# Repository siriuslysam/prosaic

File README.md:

# Prosaic
A 71-key custom mechanical keyboard design with a layout that is essentially an ANSI TKL without F-keys.

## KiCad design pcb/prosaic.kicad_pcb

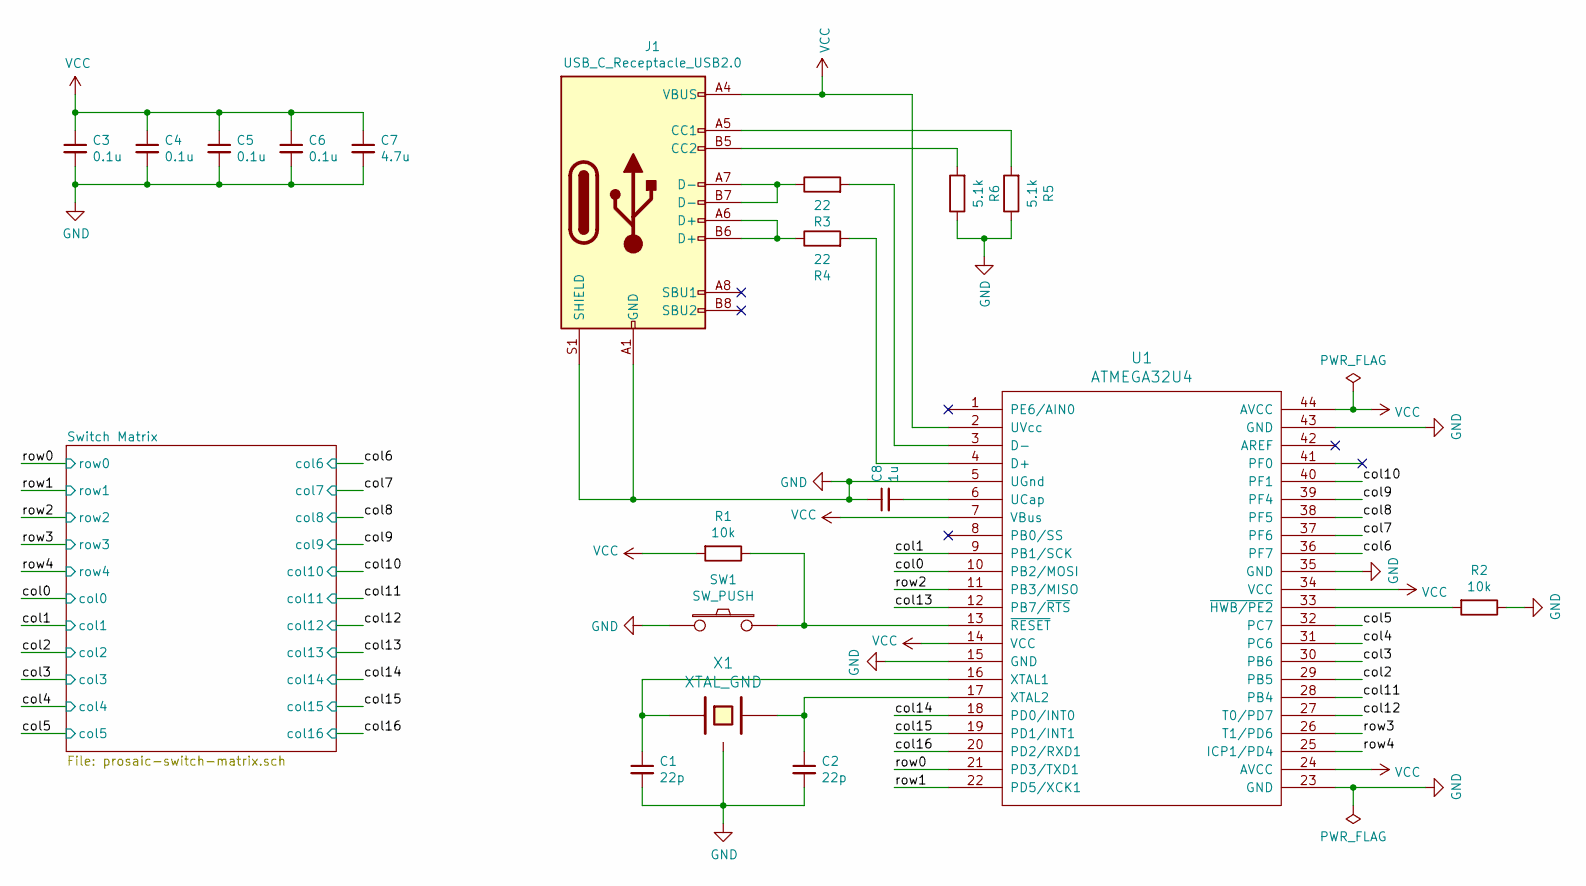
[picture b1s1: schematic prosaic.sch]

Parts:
C1, C2: 22p; C_0805_2012Metric_Pad1.15x1.40mm_HandSolder
C3, C4, C5, C6: 0.1u; C_0805_2012Metric_Pad1.15x1.40mm_HandSolder
C7: 4.7u; C_0805_2012Metric_Pad1.15x1.40mm_HandSolder
C8: 1u; C_0805_2012Metric_Pad1.15x1.40mm_HandSolder
J1: USB_C_Receptacle_USB2.0; USB_C_Receptacle_GCT_USB4085
R1, R2: 10k; R_0805_2012Metric_Pad1.15x1.40mm_HandSolder
R3, R4: 22; R_0805_2012Metric_Pad1.15x1.40mm_HandSolder
R5, R6: 5.1k; R_0805_2012Metric_Pad1.15x1.40mm_HandSolder
SW1: SW_PUSH; SW_SPST_TL3342
U1: ATMEGA32U4; TQFP-44_10x10mm_P0.8mm
X1: XTAL_GND; FA-238

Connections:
/col0: U1.10 (PB2/MOSI); also elsewhere on the board
/col1: U1.9 (PB1/SCK); also elsewhere on the board
/col2: U1.29 (PB5); also elsewhere on the board
/col3: U1.30 (PB6); also elsewhere on the board
/col4: U1.31 (PC6); also elsewhere on the board
/col5: U1.32 (PC7); also elsewhere on the board
/col6: U1.36 (PF7); also elsewhere on the board
/col7: U1.37 (PF6); also elsewhere on the board
/col8: U1.38 (PF5); also elsewhere on the board
/col9: U1.39 (PF4); also elsewhere on the board
/col10: U1.40 (PF1); also elsewhere on the board
/col11: U1.28 (PB4); also elsewhere on the board
/col12: U1.27 (T0/PD7); also elsewhere on the board
/col13: U1.12 (PB7/~RTS); also elsewhere on the board
/col14: U1.18 (PD0/INT0); also elsewhere on the board
/col15: U1.19 (PD1/INT1); also elsewhere on the board
/col16: U1.20 (PD2/RXD1); also elsewhere on the board
/row0: U1.21 (PD3/TXD1); also elsewhere on the board
/row1: U1.22 (PD5/XCK1); also elsewhere on the board
/row2: U1.11 (PB3/MISO); also elsewhere on the board
/row3: U1.26 (T1/PD6); also elsewhere on the board
/row4: U1.25 (ICP1/PD4); also elsewhere on the board
GND: C1.2, C2.2, C3.2, C4.2, C5.2, C6.2, C7.2, C8.1, J1.A1 (GND), J1.A12 (GND), J1.B1 (GND), J1.B12 (GND), J1.S1 (SHIELD), R2.1, R5.1, R6.1, SW1.1, U1.5 (UGnd), U1.15 (GND), U1.23 (GND), U1.35 (GND), U1.43 (GND), X1.3
unnamed: C1.1, U1.16 (XTAL1), X1.1
unnamed: C2.1, U1.17 (XTAL2), X1.2
unnamed: C8.2, U1.6 (UCap)
unnamed: J1.A5 (CC1), R5.2
unnamed: J1.A6 (D+), J1.B6 (D+), R4.1
unnamed: J1.A7 (D-), J1.B7 (D-), R3.1
unnamed: J1.B5 (CC2), R6.2
unnamed: R1.1, SW1.2, U1.13 (~RESET)
unnamed: R2.2, U1.33 (~HWB/PE2)
unnamed: R3.2, U1.3 (D-)
unnamed: R4.2, U1.4 (D+)
VCC: C3.1, C4.1, C5.1, C6.1, C7.1, J1.A4 (VBUS), J1.A9 (VBUS), J1.B4 (VBUS), J1.B9 (VBUS), R1.2, U1.2 (UVcc), U1.7 (VBus), U1.14 (VCC), U1.24 (AVCC), U1.34 (VCC), U1.44 (AVCC)

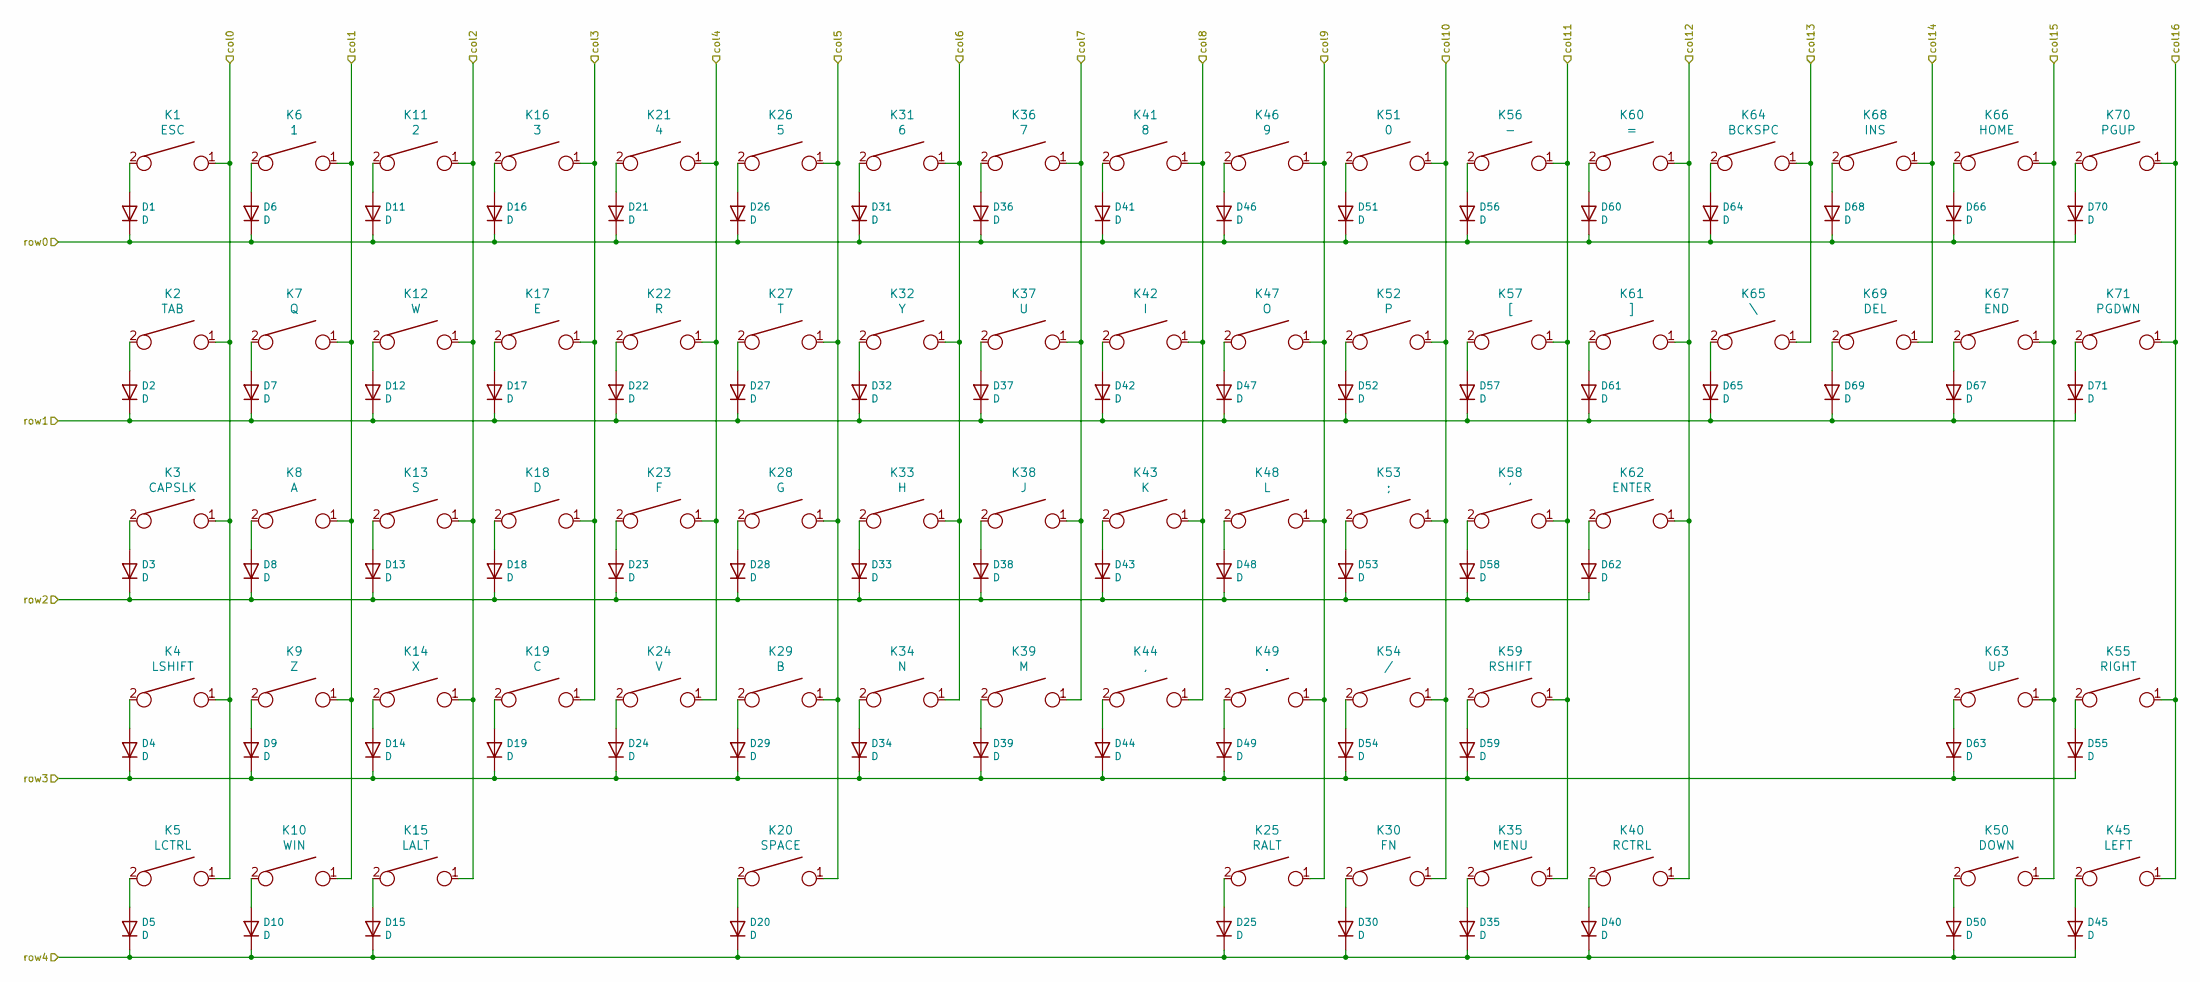
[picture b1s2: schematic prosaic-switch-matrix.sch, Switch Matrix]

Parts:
D1, D2, D3, D4, D5, D6, D7, D8, D9, D10, D11, D12, D13, D14, D15, D16, D17, D18, D19, D20, D21, D22, D23, D24, D25, D26, D27, D28, D29, D30, D31, D32, D33, D34, D35, D36, D37, D38, D39, D40, D41, D42, D43, D44, D45, D46, D47, D48, D49, D50, D51, D52, D53, D54, D55, D56, D57, D58, D59, D60, D61, D62, D63, D64, D65, D66, D67, D68, D69, D70, D71: D; D_SOD123_axial
K1: ESC; Mx_Alps_100
K2: TAB; Mx_Alps_150
K3: CAPSLK; Mx_Alps_175
K4: LSHIFT; Mx_Alps_225
K5: LCTRL; Mx_Alps_125
K6: 1; Mx_Alps_100
K7: Q; Mx_Alps_100
K8: A; Mx_Alps_100
K9: Z; Mx_Alps_100
K10: WIN; Mx_Alps_125
K11: 2; Mx_Alps_100
K12: W; Mx_Alps_100
K13: S; Mx_Alps_100
K14: X; Mx_Alps_100
K15: LALT; Mx_Alps_125
K16: 3; Mx_Alps_100
K17: E; Mx_Alps_100
K18: D; Mx_Alps_100
K19: C; Mx_Alps_100
K20: SPACE; Mx_Alps_625_reverse
K21: 4; Mx_Alps_100
K22: R; Mx_Alps_100
K23: F; Mx_Alps_100
K24: V; Mx_Alps_100
K25: RALT; Mx_Alps_125
K26: 5; Mx_Alps_100
K27: T; Mx_Alps_100
K28: G; Mx_Alps_100
K29: B; Mx_Alps_100
K30: FN; Mx_Alps_125
K31: 6; Mx_Alps_100
K32: Y; Mx_Alps_100
K33: H; Mx_Alps_100
K34: N; Mx_Alps_100
K35: MENU; Mx_Alps_125
K36: 7; Mx_Alps_100
K37: U; Mx_Alps_100
K38: J; Mx_Alps_100
K39: M; Mx_Alps_100
K40: RCTRL; Mx_Alps_125
K41: 8; Mx_Alps_100
K42: I; Mx_Alps_100
K43: K; Mx_Alps_100
K44: ,; Mx_Alps_100
K45: LEFT; Mx_Alps_100
K46: 9; Mx_Alps_100
K47: O; Mx_Alps_100
K48: L; Mx_Alps_100
K49: .; Mx_Alps_100
K50: DOWN; Mx_Alps_100
K51: 0; Mx_Alps_100
K52: P; Mx_Alps_100
K53: ;; Mx_Alps_100
K54: /; Mx_Alps_100
K55: RIGHT; Mx_Alps_100
K56: -; Mx_Alps_100
K57: [; Mx_Alps_100
K58: '; Mx_Alps_100
K59: RSHIFT; Mx_Alps_275
K60: =; Mx_Alps_100
K61: ]; Mx_Alps_100
K62: ENTER; Mx_Alps_225
K63: UP; Mx_Alps_100
K64: BCKSPC; Mx_Alps_200
K65: \\; Mx_Alps_150
K66: HOME; Mx_Alps_100
K67: END; Mx_Alps_100
K68: INS; Mx_Alps_100
K69: DEL; Mx_Alps_100
K70: PGUP; Mx_Alps_100
K71: PGDWN; Mx_Alps_100

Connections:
/col0: K1.1, K2.1, K3.1, K4.1, K5.1; also elsewhere on the board
/col1: K6.1, K7.1, K8.1, K9.1, K10.1; also elsewhere on the board
/col2: K11.1, K12.1, K13.1, K14.1, K15.1; also elsewhere on the board
/col3: K16.1, K17.1, K18.1, K19.1; also elsewhere on the board
/col4: K21.1, K22.1, K23.1, K24.1; also elsewhere on the board
/col5: K20.1, K26.1, K27.1, K28.1, K29.1; also elsewhere on the board
/col6: K31.1, K32.1, K33.1, K34.1; also elsewhere on the board
/col7: K36.1, K37.1, K38.1, K39.1; also elsewhere on the board
/col8: K41.1, K42.1, K43.1, K44.1; also elsewhere on the board
/col9: K25.1, K46.1, K47.1, K48.1, K49.1; also elsewhere on the board
/col10: K30.1, K51.1, K52.1, K53.1, K54.1; also elsewhere on the board
/col11: K35.1, K56.1, K57.1, K58.1, K59.1; also elsewhere on the board
/col12: K40.1, K60.1, K61.1, K62.1; also elsewhere on the board
/col13: K64.1, K65.1; also elsewhere on the board
/col14: K68.1, K69.1; also elsewhere on the board
/col15: K50.1, K63.1, K66.1, K67.1; also elsewhere on the board
/col16: K45.1, K55.1, K70.1, K71.1; also elsewhere on the board
/row0: D1.1 (K), D6.1 (K), D11.1 (K), D16.1 (K), D21.1 (K), D26.1 (K), D31.1 (K), D36.1 (K), D41.1 (K), D46.1 (K), D51.1 (K), D56.1 (K), D60.1 (K), D64.1 (K), D66.1 (K), D68.1 (K), D70.1 (K); also elsewhere on the board
/row1: D2.1 (K), D7.1 (K), D12.1 (K), D17.1 (K), D22.1 (K), D27.1 (K), D32.1 (K), D37.1 (K), D42.1 (K), D47.1 (K), D52.1 (K), D57.1 (K), D61.1 (K), D65.1 (K), D67.1 (K), D69.1 (K), D71.1 (K); also elsewhere on the board
/row2: D3.1 (K), D8.1 (K), D13.1 (K), D18.1 (K), D23.1 (K), D28.1 (K), D33.1 (K), D38.1 (K), D43.1 (K), D48.1 (K), D53.1 (K), D58.1 (K), D62.1 (K); also elsewhere on the board
/row3: D4.1 (K), D9.1 (K), D14.1 (K), D19.1 (K), D24.1 (K), D29.1 (K), D34.1 (K), D39.1 (K), D44.1 (K), D49.1 (K), D54.1 (K), D55.1 (K), D59.1 (K), D63.1 (K); also elsewhere on the board
/row4: D5.1 (K), D10.1 (K), D15.1 (K), D20.1 (K), D25.1 (K), D30.1 (K), D35.1 (K), D40.1 (K), D45.1 (K), D50.1 (K); also elsewhere on the board
unnamed: D1.2 (A), K1.2
unnamed: D2.2 (A), K2.2
unnamed: D3.2 (A), K3.2
unnamed: D4.2 (A), K4.2
unnamed: D5.2 (A), K5.2
unnamed: D6.2 (A), K6.2
unnamed: D7.2 (A), K7.2
unnamed: D8.2 (A), K8.2
unnamed: D9.2 (A), K9.2
unnamed: D10.2 (A), K10.2
unnamed: D11.2 (A), K11.2
unnamed: D12.2 (A), K12.2
unnamed: D13.2 (A), K13.2
unnamed: D14.2 (A), K14.2
unnamed: D15.2 (A), K15.2
unnamed: D16.2 (A), K16.2
unnamed: D17.2 (A), K17.2
unnamed: D18.2 (A), K18.2
unnamed: D19.2 (A), K19.2
unnamed: D20.2 (A), K20.2
unnamed: D21.2 (A), K21.2
unnamed: D22.2 (A), K22.2
unnamed: D23.2 (A), K23.2
unnamed: D24.2 (A), K24.2
unnamed: D25.2 (A), K25.2
unnamed: D26.2 (A), K26.2
unnamed: D27.2 (A), K27.2
unnamed: D28.2 (A), K28.2
unnamed: D29.2 (A), K29.2
unnamed: D30.2 (A), K30.2
unnamed: D31.2 (A), K31.2
unnamed: D32.2 (A), K32.2
unnamed: D33.2 (A), K33.2
unnamed: D34.2 (A), K34.2
unnamed: D35.2 (A), K35.2
unnamed: D36.2 (A), K36.2
unnamed: D37.2 (A), K37.2
unnamed: D38.2 (A), K38.2
unnamed: D39.2 (A), K39.2
unnamed: D40.2 (A), K40.2
unnamed: D41.2 (A), K41.2
unnamed: D42.2 (A), K42.2
unnamed: D43.2 (A), K43.2
unnamed: D44.2 (A), K44.2
unnamed: D45.2 (A), K45.2
unnamed: D46.2 (A), K46.2
unnamed: D47.2 (A), K47.2
unnamed: D48.2 (A), K48.2
unnamed: D49.2 (A), K49.2
unnamed: D50.2 (A), K50.2
unnamed: D51.2 (A), K51.2
unnamed: D52.2 (A), K52.2
unnamed: D53.2 (A), K53.2
unnamed: D54.2 (A), K54.2
unnamed: D55.2 (A), K55.2
unnamed: D56.2 (A), K56.2
unnamed: D57.2 (A), K57.2
unnamed: D58.2 (A), K58.2
unnamed: D59.2 (A), K59.2
unnamed: D60.2 (A), K60.2
unnamed: D61.2 (A), K61.2
unnamed: D62.2 (A), K62.2
unnamed: D63.2 (A), K63.2
unnamed: D64.2 (A), K64.2
unnamed: D65.2 (A), K65.2
unnamed: D66.2 (A), K66.2
unnamed: D67.2 (A), K67.2
unnamed: D68.2 (A), K68.2
unnamed: D69.2 (A), K69.2
unnamed: D70.2 (A), K70.2
unnamed: D71.2 (A), K71.2

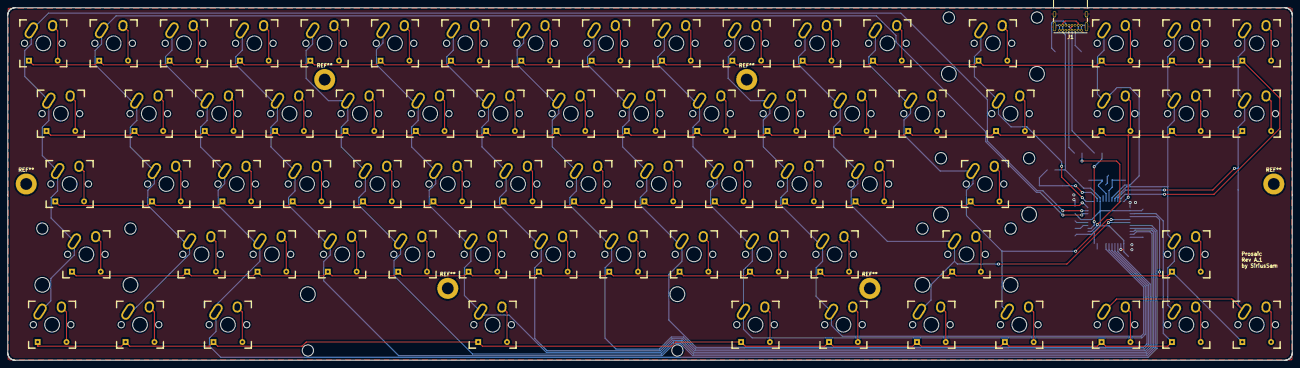
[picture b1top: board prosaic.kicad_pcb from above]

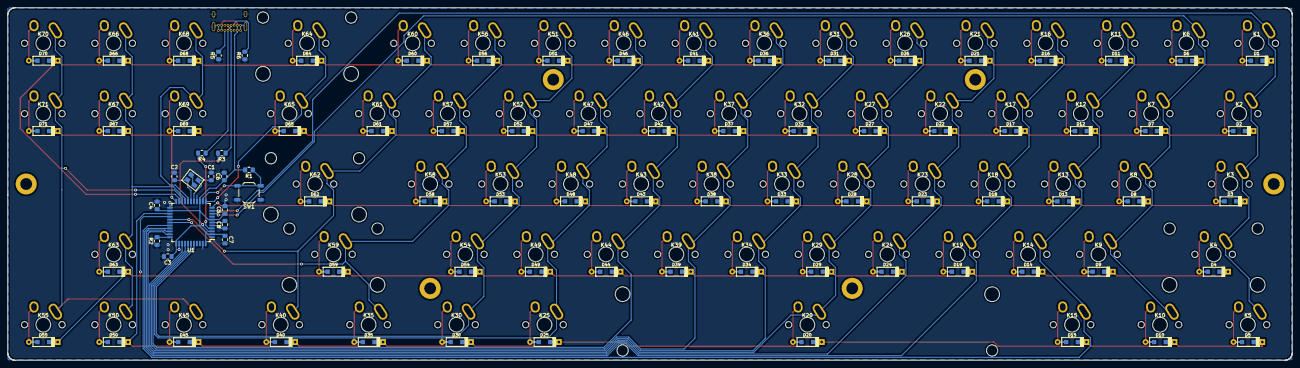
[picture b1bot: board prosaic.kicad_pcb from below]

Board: 2 copper layers, 347.9 x 95.5 mm, 160 parts (88 on the bottom side), 106 nets.

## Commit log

2020-07-23 Rev - of keyboard PCB
2020-07-24 Added mounting plate CAD
2020-07-28 Added case CAD and assembly
2020-07-29 Adjusted tilt angle to 5 degrees
2020-07-29 Made moutning hole rearrangements
2020-07-29 Updated gitignore for .net
2020-07-30 WIP: Ready for stabilizer verification
2020-08-02 Completed revision with new PCB layout
2020-08-04 Made trace change around crystal; updated case cad
2020-08-07 Rerouted VCC trace
2020-08-09 Opened up feet holes
2020-08-09 Fixed stabilizer switch plate
2020-08-10 Added case drawings
2020-08-13 Included a picture of the CAD assembly
